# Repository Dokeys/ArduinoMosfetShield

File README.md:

# ArduinoMosfetShield

## Description

Arduino Shield with Mosfets, Buttons and connectors.

**Project currently in development.**

## Tools

Developed with [KiCad EDA](https://www.kicad.org/).

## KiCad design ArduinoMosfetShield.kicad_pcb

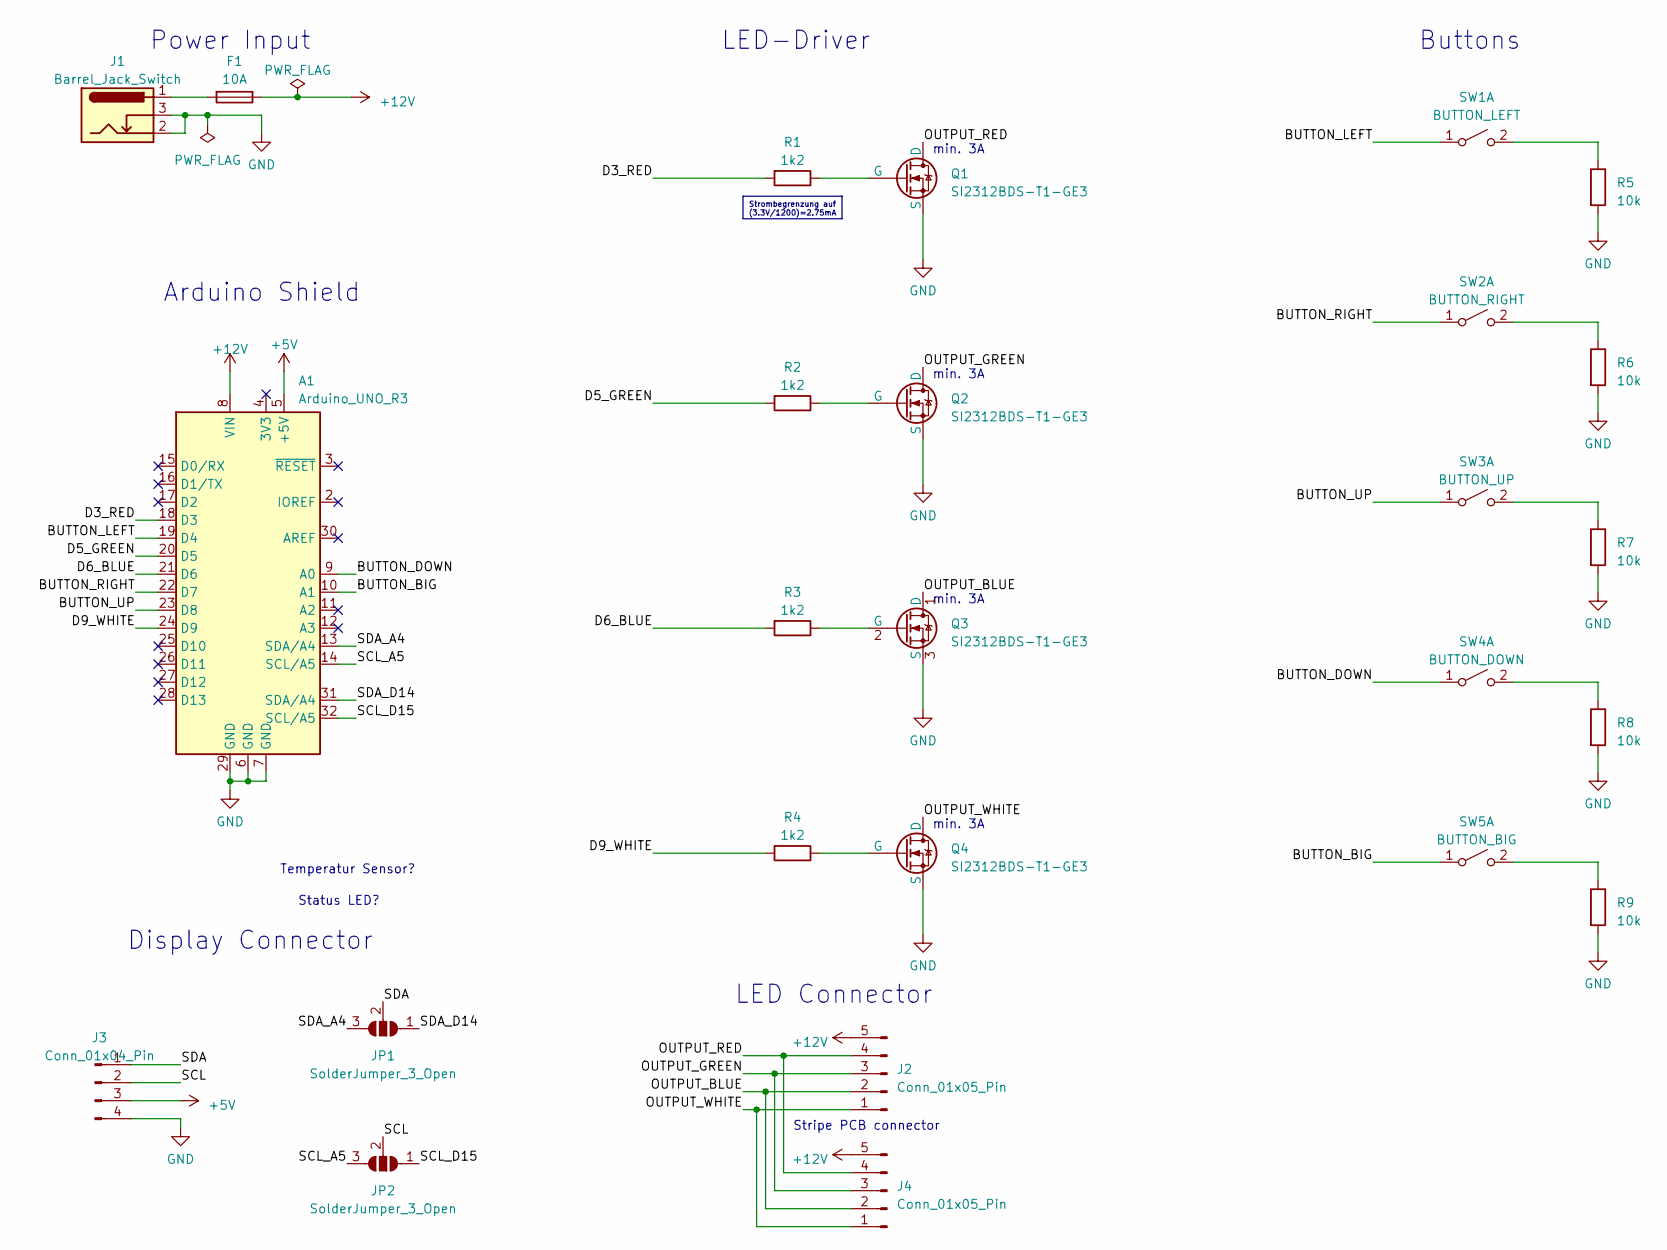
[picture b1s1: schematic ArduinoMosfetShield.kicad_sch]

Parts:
A1: Arduino_UNO_R3
F1: 10A; 451-453_Series_Fuse; LCSC C44479
J1: Barrel_Jack_Switch; BarrelJack_GCT_DCJ200-10-A_Horizontal
J2: Conn_01x05_Pin; PinHeader_1x05_P2.54mm_Vertical
J3: Conn_01x04_Pin; PinHeader_1x04_P2.54mm_Vertical
J4: Conn_01x05_Pin; RGBW_Stripe_PCB_Solder_Connector
JP1, JP2: SolderJumper_3_Open; SolderJumper-3_P1.3mm_Open_RoundedPad1.0x1.5mm_NumberLabels
Q1, Q2, Q3, Q4: SI2312BDS-T1-GE3; SOT-23; LCSC C10490
R1, R2, R3, R4: 1k2; R_0603_1608Metric; LCSC C22765
R5, R6, R7, R8, R9: 10k; R_0603_1608Metric; LCSC C116677
SW1: BUTTON_LEFT; SW_PUSH_6mm
SW2: BUTTON_RIGHT; SW_PUSH_6mm
SW3: BUTTON_UP; SW_PUSH_6mm
SW4: BUTTON_DOWN; SW_PUSH_6mm
SW5: BUTTON_BIG; SW_PUSH-12mm

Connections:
+5V: A1.5 (+5V), J3.3
+12V: A1.8 (VIN), F1.1, J2.5, J4.5
/BUTTON_BIG: A1.10 (A1), SW5.1 (A)
/BUTTON_DOWN: A1.9 (A0), SW4.1 (A)
/BUTTON_LEFT: A1.19 (D4), SW1.1 (A)
/BUTTON_RIGHT: A1.22 (D7), SW2.1 (A)
/BUTTON_UP: A1.23 (D8), SW3.1 (A)
/D3_RED: A1.18 (D3), R1.2
/D5_GREEN: A1.20 (D5), R2.2
/D6_BLUE: A1.21 (D6), R3.2
/D9_WHITE: A1.24 (D9), R4.2
/OUTPUT_BLUE: J2.2, J4.2, Q3.1 (D)
/OUTPUT_GREEN: J2.3, J4.3, Q2.1 (D)
/OUTPUT_RED: J2.4, J4.4, Q1.1 (D)
/OUTPUT_WHITE: J2.1, J4.1, Q4.1 (D)
/SCL: J3.2, JP2.2 (C)
/SCL_A5: A1.14 (SCL/A5), JP2.3 (B)
/SCL_D15: A1.32 (SCL/A5), JP2.1 (A)
/SDA: J3.1, JP1.2 (C)
/SDA_A4: A1.13 (SDA/A4), JP1.3 (B)
/SDA_D14: A1.31 (SDA/A4), JP1.1 (A)
GND: A1.6 (GND), A1.7 (GND), A1.29 (GND), J1.2, J1.3, J3.4, Q1.3 (S), Q2.3 (S), Q3.3 (S), Q4.3 (S), R5.2, R6.2, R7.2, R8.2, R9.2
unnamed: F1.2, J1.1
unnamed: Q1.2 (G), R1.1
unnamed: Q2.2 (G), R2.1
unnamed: Q3.2 (G), R3.1
unnamed: Q4.2 (G), R4.1
unnamed: R5.1, SW1.2 (B)
unnamed: R6.1, SW2.2 (B)
unnamed: R7.1, SW3.2 (B)
unnamed: R8.1, SW4.2 (B)
unnamed: R9.1, SW5.2 (B)

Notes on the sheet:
Strombegrenzung auf (3.3V/1200)=2.75mA
LED-Driver
min. 3A
Buttons
Stripe PCB connector
LED Connector
Arduino Shield
Status LED?
Temperatur Sensor?
Power Input
Display Connector

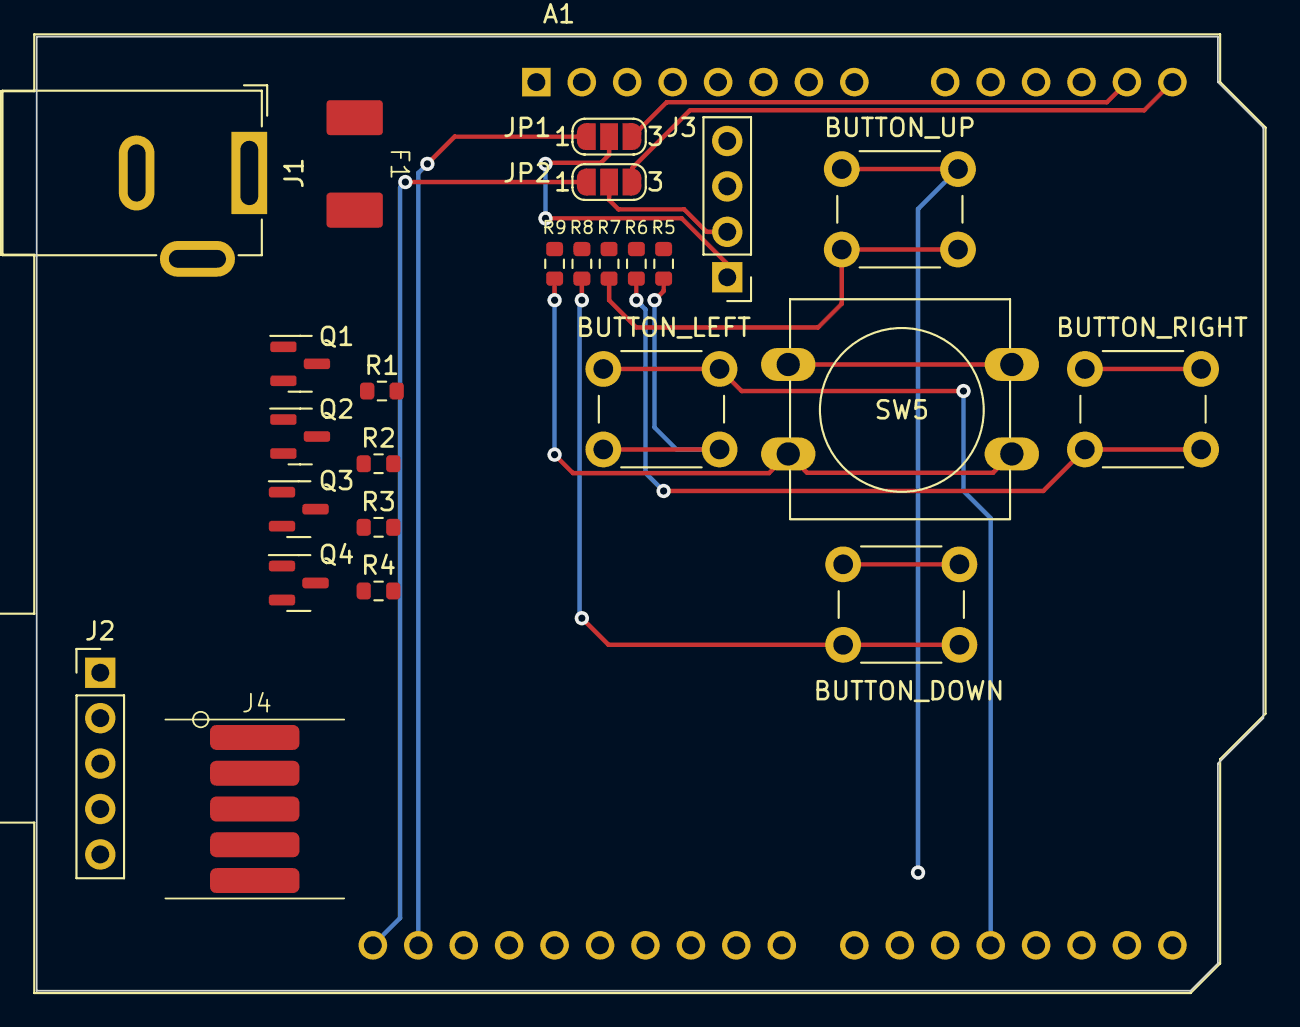
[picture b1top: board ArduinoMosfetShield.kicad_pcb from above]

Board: 2 copper layers, 68.6 x 53.3 mm, 26 parts (0 on the bottom side), 32 nets.

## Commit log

2023-11-22 Initial commit with Schematic and PCB layout.
2023-11-22 Added short project description.
2023-11-22 Added KiCad information.
